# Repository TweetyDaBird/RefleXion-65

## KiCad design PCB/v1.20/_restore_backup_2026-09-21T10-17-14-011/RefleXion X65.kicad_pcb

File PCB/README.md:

# RefleXion X65

# Change Log:
- v1.00 - Initial Prototype
  - Never released.

- v1.10 - First Release
  - Total redesign for onboard RP2040 MCU
  
- v1.15 - Second Prototype
  - Never Released.
  
- v1.20 - Second Release
  - Refactored USB footprint.
  - Refactored encoder footprints.
  - Refactored switch footprints with reinforced pads(larger via).
  - Added RGB selection from Glow to Per-Key with switch.
  - Added solder/jumper to select thumb RGB layout.

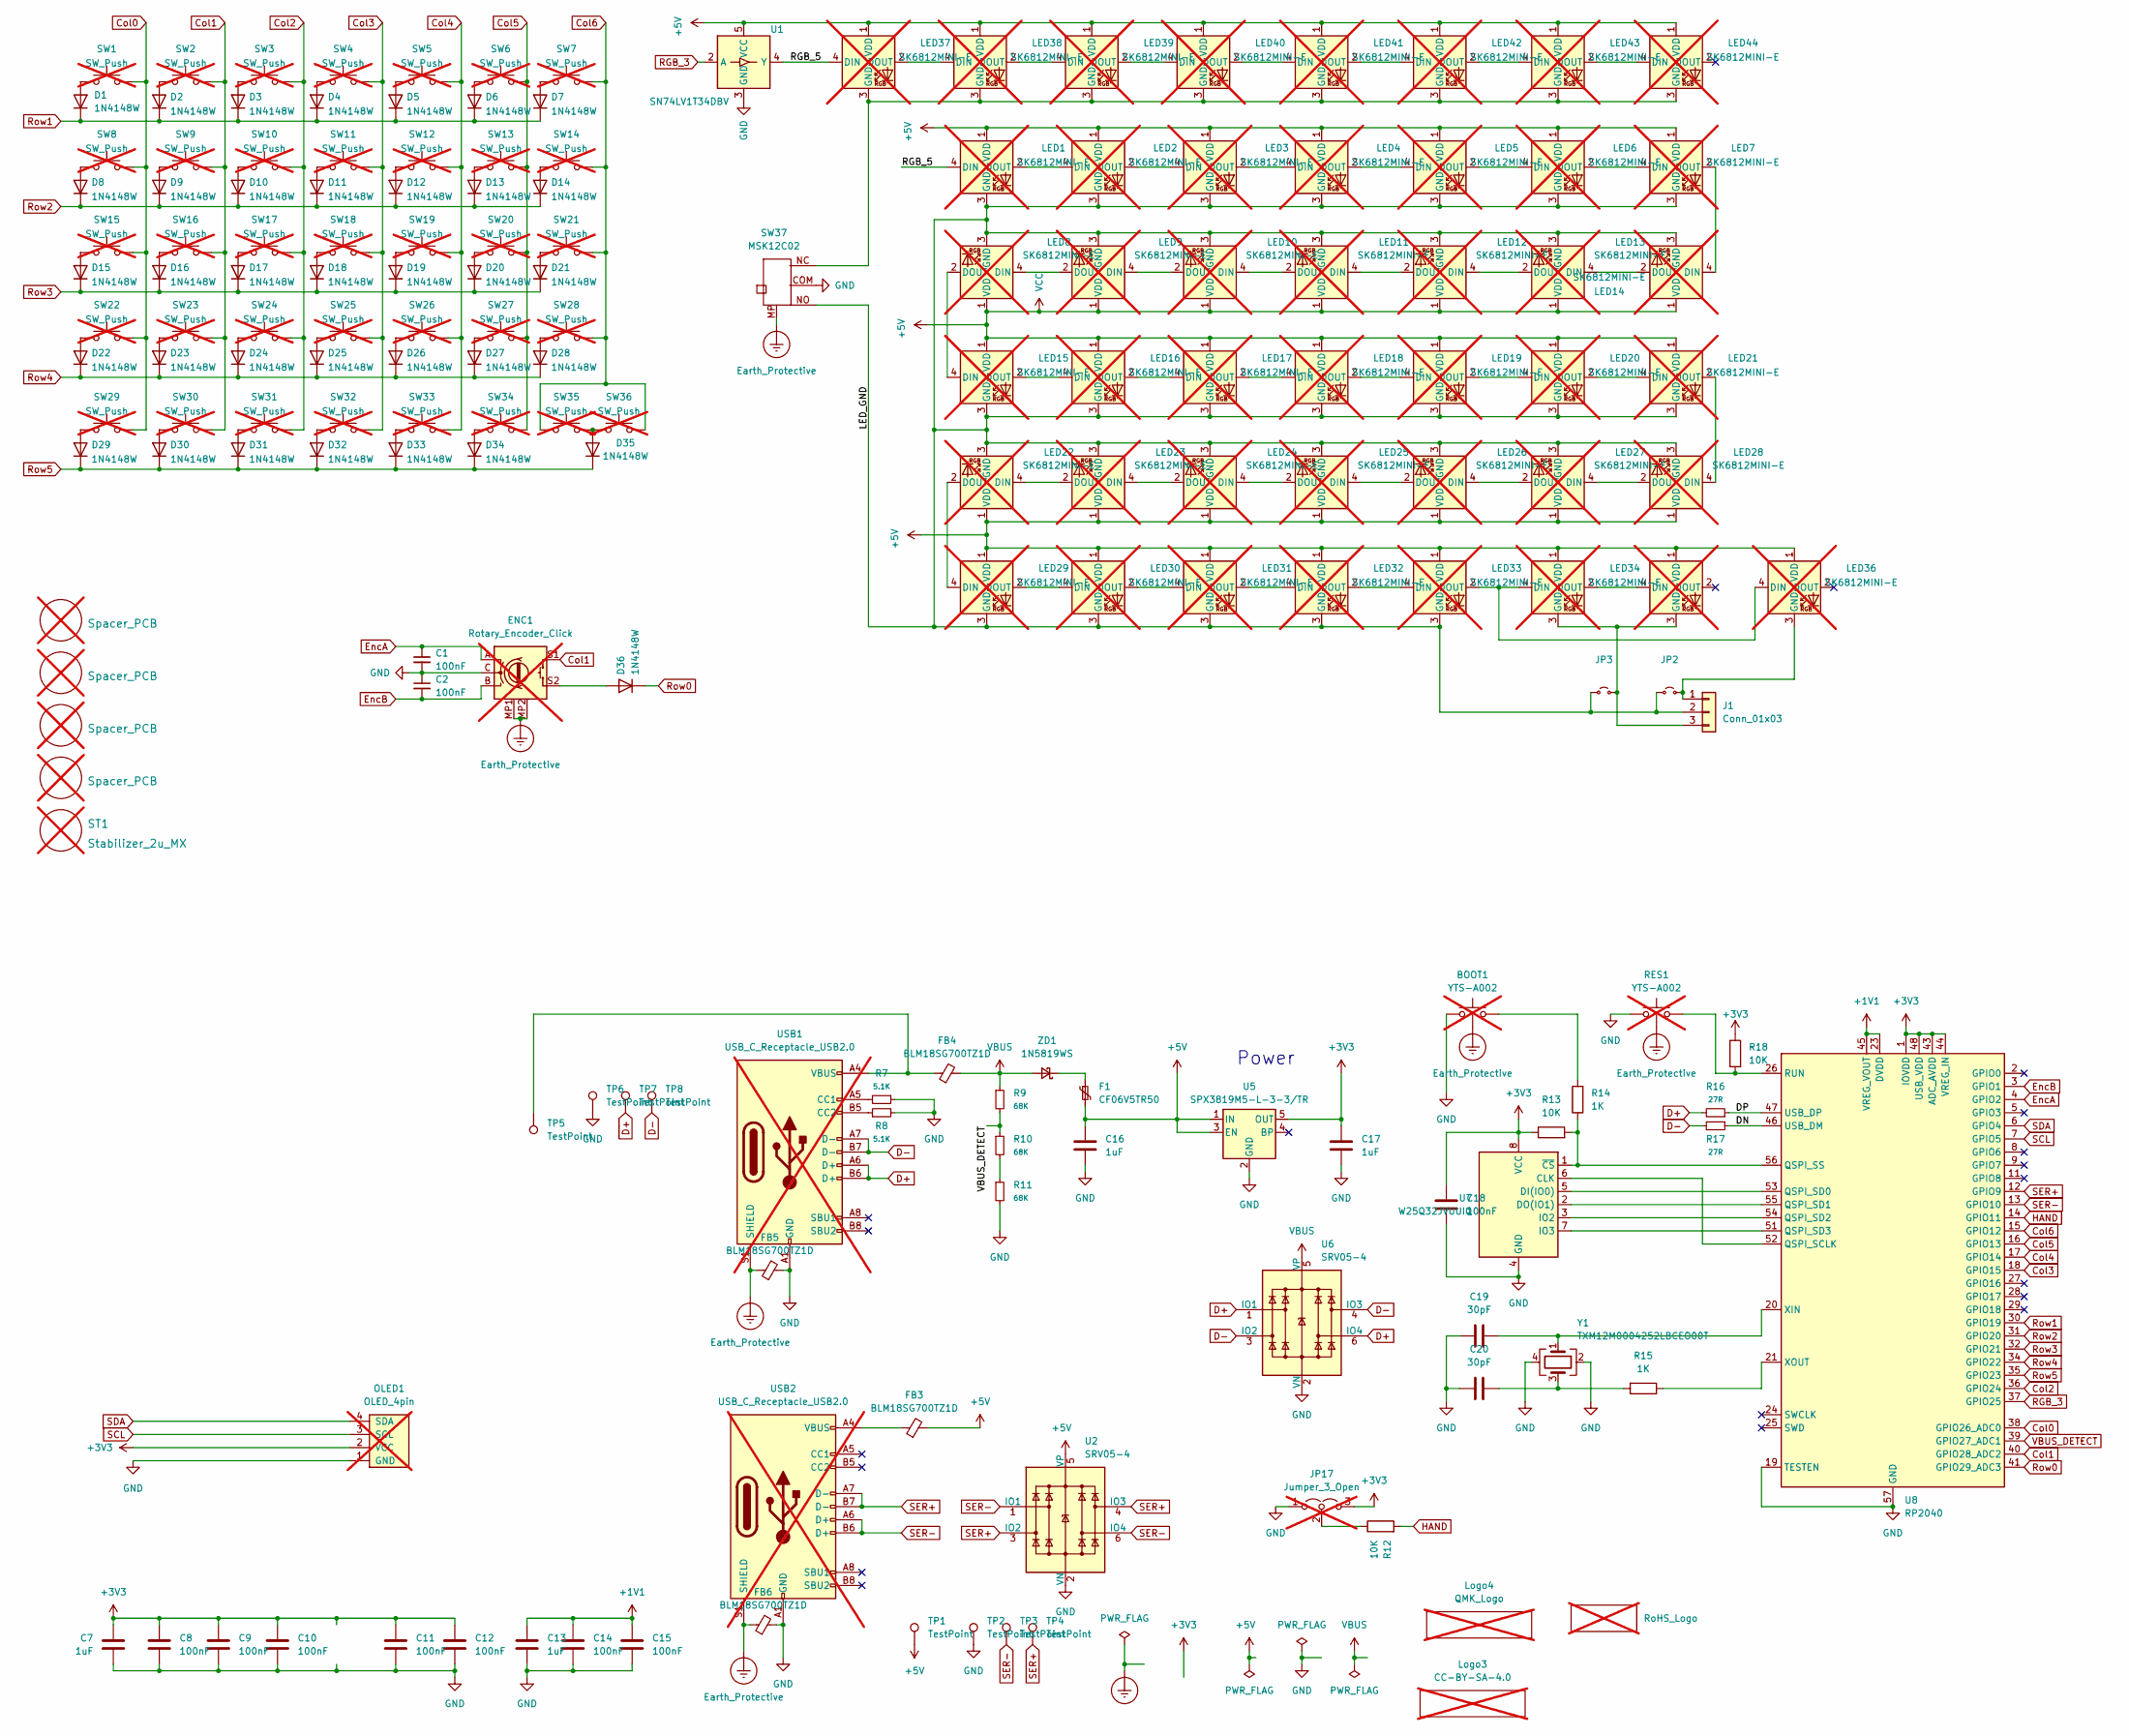
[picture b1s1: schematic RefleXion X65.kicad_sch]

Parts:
BOOT1: YTS-A002; LCSC C2910650; not fitted
C1, C2, C8, C9, C10, C11, C12, C14, C15, C18: 100nF; C_0402_1005Metric; LCSC C1525
C7, C13, C16, C17: 1uF; C_0402_1005Metric; LCSC C52923
C19, C20: 30pF; C_0402_1005Metric; LCSC C1570
D1, D2, D3, D4, D5, D6, D7, D8, D9, D10, D11, D12, D13, D14, D15, D16, D17, D18, D19, D20, D21, D22, D23, D24, D25, D26, D27, D28, D29, D30, D31, D32, D33, D34, D35, D36: 1N4148W; D_SOD-323_HandSoldering; LCSC C81598
ENC1: Rotary_Encoder_Click; Encoder_Alps_EC11E_Small; not fitted
F1: CF06V5TR50; R_0603_1608Metric; LCSC C163116
FB3, FB4, FB5, FB6: BLM18SG700TZ1D; C_0603_1608Metric_Pad1.08x0.95mm_HandSolder; LCSC C1002
H1, H2, H3, H4: Spacer_PCB; Spacer PCB hole; not fitted
J1: Conn_01x03; PinHeader_1x03_P1.27mm_Horizontal
JP2, JP3: Jumper_2_Small_Open; Jumper_min_v2
JP17: Jumper_3_Open; SolderJumper-3_open_mini; not fitted
LED1, LED2, LED3, LED4, LED5, LED6, LED7, LED8, LED9, LED10, LED11, LED12, LED13, LED14, LED15, LED16, LED17, LED18, LED19, LED20, LED21, LED22, LED23, LED24, LED25, LED26, LED27, LED28, LED29, LED30, LED31, LED32, LED33: SK6812MINI-E; MX_SK6812MINI-E_REVERSIBLE; not fitted
LED34, LED35, LED36, LED37, LED38, LED39, LED40, LED41, LED42, LED43, LED44: SK6812MINI-E; MX_SK6812MINI-E_REVERSIBLE_special; not fitted
Logo1: RoHS_Logo; RoHs; not fitted
Logo3: CC-BY-SA-4.0; CC_BY_SA_40_line; not fitted
Logo4: QMK_Logo; Powered_by_QMK; not fitted
OLED1: OLED_4pin; SSD1306-0.91-OLED-4pin-128x32 doublesided; not fitted
R7, R8: 5.1K; R_0402_1005Metric; LCSC C25905
R9, R10, R11: 68K; R_0402_1005Metric; LCSC C137947
R12, R13, R18: 10K; R_0402_1005Metric; LCSC C25744
R14, R15: 1K; R_0402_1005Metric; LCSC C11702
R16, R17: 27R; R_0402_1005Metric; LCSC C321419
RES1: YTS-A002; LCSC C2910650; not fitted
ST1: Stabilizer_2u_MX; Stabilizer_Cherry_MX_2.00u; not fitted
SW1, SW2, SW3, SW4, SW5, SW6, SW7, SW8, SW9, SW10, SW11, SW12, SW13, SW14, SW15, SW16, SW17, SW18, SW19, SW20, SW21, SW22, SW23, SW24, SW25, SW26, SW27, SW28, SW29, SW30, SW31, SW32, SW33, SW34, SW35, SW36: SW_Push; SW_MX_HotSwap_Reversible_reinforced; not fitted
SW37: MSK12C02
TP1, TP2, TP3, TP4, TP5, TP6, TP7, TP8: TestPoint; TestPoint_Pad_D1.0mm
U1: SN74LV1T34DBV; SOT-23-5; LCSC C100024
U2, U6: SRV05-4; SOT-23-6; LCSC C7420376
U5: SPX3819M5-L-3-3/TR; SOT-23-5; LCSC C9055
U7: W25Q32JVUUIQ; USON-8_4x3mm_P0.8mm; LCSC C2999380
U8: RP2040; QFN-56-1EP_7x7mm_P0.4mm_EP3.2x3.2mm_ThermalVias; LCSC C2040
USB1: USB_C_Receptacle_USB2.0; HRO_TYPE-C-31-M-12_double_sided; LCSC C963373; not fitted
USB2: USB_C_Receptacle_USB2.0; HRO_TYPE-C-31-M-12_double_sided_serial link; LCSC C963373; not fitted
Y1: TXM12M0004252LBCEO00T; Crystal_SMD_2520-4Pin_2.5x2.0mm; LCSC C284156
ZD1: 1N5819WS; D_SOD-323F; LCSC C191023

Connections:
+1V1: C13.1, C14.1, C15.1, U8.23 (DVDD), U8.45 (VREG_VOUT), U8.50 (DVDD)
+3V3: C7.1, C8.1, C9.1, C10.1, C11.1, C12.1, C17.1, C18.1, JP17.3 (B), OLED1.2 (VCC), R13.1, R18.1, U5.5 (OUT), U7.8 (VCC), U8.1 (IOVDD), U8.10 (IOVDD), U8.22 (IOVDD), U8.33 (IOVDD), U8.42 (IOVDD), U8.43 (ADC_AVDD), U8.44 (VREG_IN), U8.48 (USB_VDD), U8.49 (IOVDD)
+5V: C16.1, F1.2, FB3.2, LED1.1 (VDD), LED2.1 (VDD), LED3.1 (VDD), LED4.1 (VDD), LED5.1 (VDD), LED6.1 (VDD), LED7.1 (VDD), LED8.1 (VDD), LED9.1 (VDD), LED10.1 (VDD), LED11.1 (VDD), LED12.1 (VDD), LED13.1 (VDD), LED14.1 (VDD), LED15.1 (VDD), LED16.1 (VDD), LED17.1 (VDD), LED18.1 (VDD), LED19.1 (VDD), LED20.1 (VDD), LED21.1 (VDD), LED22.1 (VDD), LED23.1 (VDD), LED24.1 (VDD), LED25.1 (VDD), LED26.1 (VDD), LED27.1 (VDD), LED28.1 (VDD), LED29.1 (VDD), LED30.1 (VDD), LED31.1 (VDD), LED32.1 (VDD), LED33.1 (VDD), LED34.1 (VDD), LED35.1 (VDD), LED36.1 (VDD), LED37.1 (VDD), LED38.1 (VDD), LED39.1 (VDD), LED40.1 (VDD), LED41.1 (VDD), LED42.1 (VDD), LED43.1 (VDD), LED44.1 (VDD), TP1.1 (1_1), U1.5 (VCC), U2.5 (VP), U5.1 (IN), U5.3 (EN)
/DN: R17.1, U8.46 (USB_DM)
/DP: R16.1, U8.47 (USB_DP)
/LED_GND: J1.2, JP2.1 (A), JP3.1 (A), LED1.3 (GND), LED2.3 (GND), LED3.3 (GND), LED4.3 (GND), LED5.3 (GND), LED6.3 (GND), LED7.3 (GND), LED8.3 (GND), LED9.3 (GND), LED10.3 (GND), LED11.3 (GND), LED12.3 (GND), LED13.3 (GND), LED14.3 (GND), LED15.3 (GND), LED16.3 (GND), LED17.3 (GND), LED18.3 (GND), LED19.3 (GND), LED20.3 (GND), LED21.3 (GND), LED22.3 (GND), LED23.3 (GND), LED24.3 (GND), LED25.3 (GND), LED26.3 (GND), LED27.3 (GND), LED28.3 (GND), LED29.3 (GND), LED30.3 (GND), LED31.3 (GND), LED32.3 (GND), LED33.3 (GND), SW37.NO
/RGB_5: LED1.4 (DIN), LED37.4 (DIN), U1.4 (Y)
Col0: SW1.1, SW8.1, SW15.1, SW22.1, SW29.1, U8.38 (GPIO26_ADC0)
Col1: ENC1.S1, SW2.2, SW9.2, SW16.2, SW23.2, SW30.2, U8.40 (GPIO28_ADC2)
Col2: SW3.2, SW10.2, SW17.2, SW24.2, SW31.2, U8.36 (GPIO24)
Col3: SW4.2, SW11.2, SW18.2, SW25.2, SW32.2, U8.18 (GPIO15)
Col4: SW5.2, SW12.2, SW19.2, SW26.2, SW33.2, U8.17 (GPIO14)
Col5: SW6.2, SW13.2, SW20.2, SW27.2, SW34.2, U8.16 (GPIO13)
Col6: SW7.2, SW14.2, SW21.2, SW28.2, SW35.1, SW36.2, U8.15 (GPIO12)
D+: R16.2, TP7.1 (1_1), U6.1 (IO1), U6.6 (IO4), USB1.A6 (D+), USB1.B6 (D+)
D-: R17.2, TP8.1 (1_1), U6.3 (IO2), U6.4 (IO3), USB1.A7 (D-), USB1.B7 (D-)
Earth_Protective: BOOT1.3, ENC1.MP1 (GND), ENC1.MP2 (GND), FB5.1, FB6.1, RES1.3, SW37.MP (GND), USB1.S1 (SHIELD), USB2.S1 (SHIELD)
Enc1: D1.2 (A), SW1.2
Enc2: D7.2 (A), SW7.1
EncA: C1.1, ENC1.A, U8.4 (GPIO2)
EncB: C2.2, ENC1.B, U8.3 (GPIO1)
GND: BOOT1.2, C1.2, C2.1, C7.2, C8.2, C9.2, C10.2, C11.2, C12.2, C13.2, C14.2, C15.2, C16.2, C17.2, C18.2, C19.2, C20.2, ENC1.C, FB5.2, FB6.2, JP17.1 (A), OLED1.1 (GND), R7.1, R8.2, R11.2, RES1.1, SW37.COM, TP2.1 (1_1), TP6.1 (1_1), U1.3 (GND), U2.2 (VN), U5.2 (GND), U6.2 (VN), U7.4 (GND), U8.19 (TESTEN), U8.57 (GND), USB1.A1 (GND), USB1.A12 (GND), USB1.B1 (GND), USB1.B12 (GND), USB2.A1 (GND), USB2.A12 (GND), USB2.B1 (GND), USB2.B12 (GND), Y1.2, Y1.4
HAND: R12.2, U8.14 (GPIO11)
unnamed: BOOT1.1, R14.2
unnamed: C20.1, R15.2, Y1.3
unnamed: D2.2 (A), SW2.1
unnamed: D3.2 (A), SW3.1
unnamed: D4.2 (A), SW4.1
unnamed: D5.2 (A), SW5.1
unnamed: D6.2 (A), SW6.1
unnamed: D8.2 (A), SW8.2
unnamed: D9.2 (A), SW9.1
unnamed: D10.2 (A), SW10.1
unnamed: D11.2 (A), SW11.1
unnamed: D12.2 (A), SW12.1
unnamed: D13.2 (A), SW13.1
unnamed: D14.2 (A), SW14.1
unnamed: D15.2 (A), SW15.2
unnamed: D16.2 (A), SW16.1
unnamed: D17.2 (A), SW17.1
unnamed: D18.2 (A), SW18.1
unnamed: D19.2 (A), SW19.1
unnamed: D20.2 (A), SW20.1
unnamed: D21.2 (A), SW21.1
unnamed: D22.2 (A), SW22.2
unnamed: D23.2 (A), SW23.1
unnamed: D24.2 (A), SW24.1
unnamed: D25.2 (A), SW25.1
unnamed: D26.2 (A), SW26.1
unnamed: D27.2 (A), SW27.1
unnamed: D28.2 (A), SW28.1
unnamed: D29.2 (A), SW29.2
unnamed: D30.2 (A), SW30.1
unnamed: D31.2 (A), SW31.1
unnamed: D32.2 (A), SW32.1
unnamed: D33.2 (A), SW33.1
unnamed: D34.2 (A), SW34.1
unnamed: D35.2 (A), SW35.2, SW36.1
unnamed: D36.2 (A), ENC1.S2
unnamed: FB3.1, USB2.A4 (VBUS), USB2.A9 (VBUS), USB2.B4 (VBUS), USB2.B9 (VBUS)
unnamed: FB4.1, TP5.1 (1_1), USB1.A4 (VBUS), USB1.A9 (VBUS), USB1.B4 (VBUS), USB1.B9 (VBUS)
unnamed: J1.1, JP2.2 (B), LED36.3 (GND)
unnamed: J1.3, JP3.2 (B), LED34.3 (GND), LED35.3 (GND)
unnamed: JP17.2 (C), R12.1
unnamed: LED1.2 (DOUT), LED2.4 (DIN)
unnamed: LED2.2 (DOUT), LED3.4 (DIN)
unnamed: LED3.2 (DOUT), LED4.4 (DIN)
unnamed: LED4.2 (DOUT), LED5.4 (DIN)
unnamed: LED5.2 (DOUT), LED6.4 (DIN)
unnamed: LED6.2 (DOUT), LED7.4 (DIN)
unnamed: LED8.4 (DIN), LED9.2 (DOUT)
unnamed: LED10.4 (DIN), LED11.2 (DOUT)
unnamed: LED9.4 (DIN), LED10.2 (DOUT)
unnamed: LED11.4 (DIN), LED12.2 (DOUT)
unnamed: LED12.4 (DIN), LED13.2 (DOUT)
unnamed: LED13.4 (DIN), LED14.2 (DOUT)
unnamed: LED7.2 (DOUT), LED14.4 (DIN)
unnamed: LED8.2 (DOUT), LED15.4 (DIN)
unnamed: LED15.2 (DOUT), LED16.4 (DIN)
unnamed: LED16.2 (DOUT), LED17.4 (DIN)
unnamed: LED17.2 (DOUT), LED18.4 (DIN)
unnamed: LED18.2 (DOUT), LED19.4 (DIN)
unnamed: LED19.2 (DOUT), LED20.4 (DIN)
unnamed: LED20.2 (DOUT), LED21.4 (DIN)
unnamed: LED21.2 (DOUT), LED28.4 (DIN)
unnamed: LED22.4 (DIN), LED23.2 (DOUT)
unnamed: LED22.2 (DOUT), LED29.4 (DIN)
unnamed: LED23.4 (DIN), LED24.2 (DOUT)
unnamed: LED24.4 (DIN), LED25.2 (DOUT)
unnamed: LED25.4 (DIN), LED26.2 (DOUT)
unnamed: LED26.4 (DIN), LED27.2 (DOUT)
unnamed: LED27.4 (DIN), LED28.2 (DOUT)
unnamed: LED29.2 (DOUT), LED30.4 (DIN)
unnamed: LED30.2 (DOUT), LED31.4 (DIN)
unnamed: LED31.2 (DOUT), LED32.4 (DIN)
unnamed: LED32.2 (DOUT), LED33.4 (DIN)
unnamed: LED33.2 (DOUT), LED34.4 (DIN), LED36.4 (DIN)
unnamed: LED34.2 (DOUT), LED35.4 (DIN)
unnamed: LED37.2 (DOUT), LED38.4 (DIN)
unnamed: LED37.3 (GND), LED38.3 (GND), LED39.3 (GND), LED40.3 (GND), LED41.3 (GND), LED42.3 (GND), LED43.3 (GND), LED44.3 (GND), SW37.NC
unnamed: LED38.2 (DOUT), LED39.4 (DIN)
unnamed: LED39.2 (DOUT), LED40.4 (DIN)
unnamed: LED40.2 (DOUT), LED41.4 (DIN)
unnamed: LED41.2 (DOUT), LED42.4 (DIN)
unnamed: LED42.2 (DOUT), LED43.4 (DIN)
unnamed: LED43.2 (DOUT), LED44.4 (DIN)
unnamed: R10.2, R11.1
unnamed: U7.6 (CLK), U8.52 (QSPI_SCLK)
unnamed: U7.5 (DI(IO0)), U8.53 (QSPI_SD0)
unnamed: U7.2 (DO(IO1)), U8.55 (QSPI_SD1)
unnamed: U7.3 (IO2), U8.54 (QSPI_SD2)
unnamed: U7.7 (IO3), U8.51 (QSPI_SD3)
unnamed: R13.2, R14.1, U7.1 (~CS), U8.56 (QSPI_SS)
unnamed: R18.2, RES1.2, U8.26 (RUN)
unnamed: C19.1, U8.20 (XIN), Y1.1
unnamed: R15.1, U8.21 (XOUT)
unnamed: R7.2, USB1.A5 (CC1)
unnamed: R8.1, USB1.B5 (CC2)
unnamed: F1.1, ZD1.1 (K)
RGB_3: U1.2 (A), U8.37 (GPIO25)
Row0: D36.1 (K), U8.41 (GPIO29_ADC3)
Row1: D1.1 (K), D2.1 (K), D3.1 (K), D4.1 (K), D5.1 (K), D6.1 (K), D7.1 (K), U8.30 (GPIO19)
Row2: D8.1 (K), D9.1 (K), D10.1 (K), D11.1 (K), D12.1 (K), D13.1 (K), D14.1 (K), U8.31 (GPIO20)
Row3: D15.1 (K), D16.1 (K), D17.1 (K), D18.1 (K), D19.1 (K), D20.1 (K), D21.1 (K), U8.32 (GPIO21)
Row4: D22.1 (K), D23.1 (K), D24.1 (K), D25.1 (K), D26.1 (K), D27.1 (K), D28.1 (K), U8.34 (GPIO22)
Row5: D29.1 (K), D30.1 (K), D31.1 (K), D32.1 (K), D33.1 (K), D34.1 (K), D35.1 (K), U8.35 (GPIO23)
SCL: OLED1.3 (SCL), U8.7 (GPIO5)
SDA: OLED1.4 (SDA), U8.6 (GPIO4)
SER+: TP4.1 (1_1), U2.3 (IO2), U2.4 (IO3), U8.12 (GPIO9), USB2.A7 (D-), USB2.B7 (D-)
SER-: TP3.1 (1_1), U2.1 (IO1), U2.6 (IO4), U8.13 (GPIO10), USB2.A6 (D+), USB2.B6 (D+)
VBUS: FB4.2, R9.1, U6.5 (VP), ZD1.2 (A)
VBUS_DETECT: R9.2, R10.1, U8.39 (GPIO27_ADC1)

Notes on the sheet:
Power

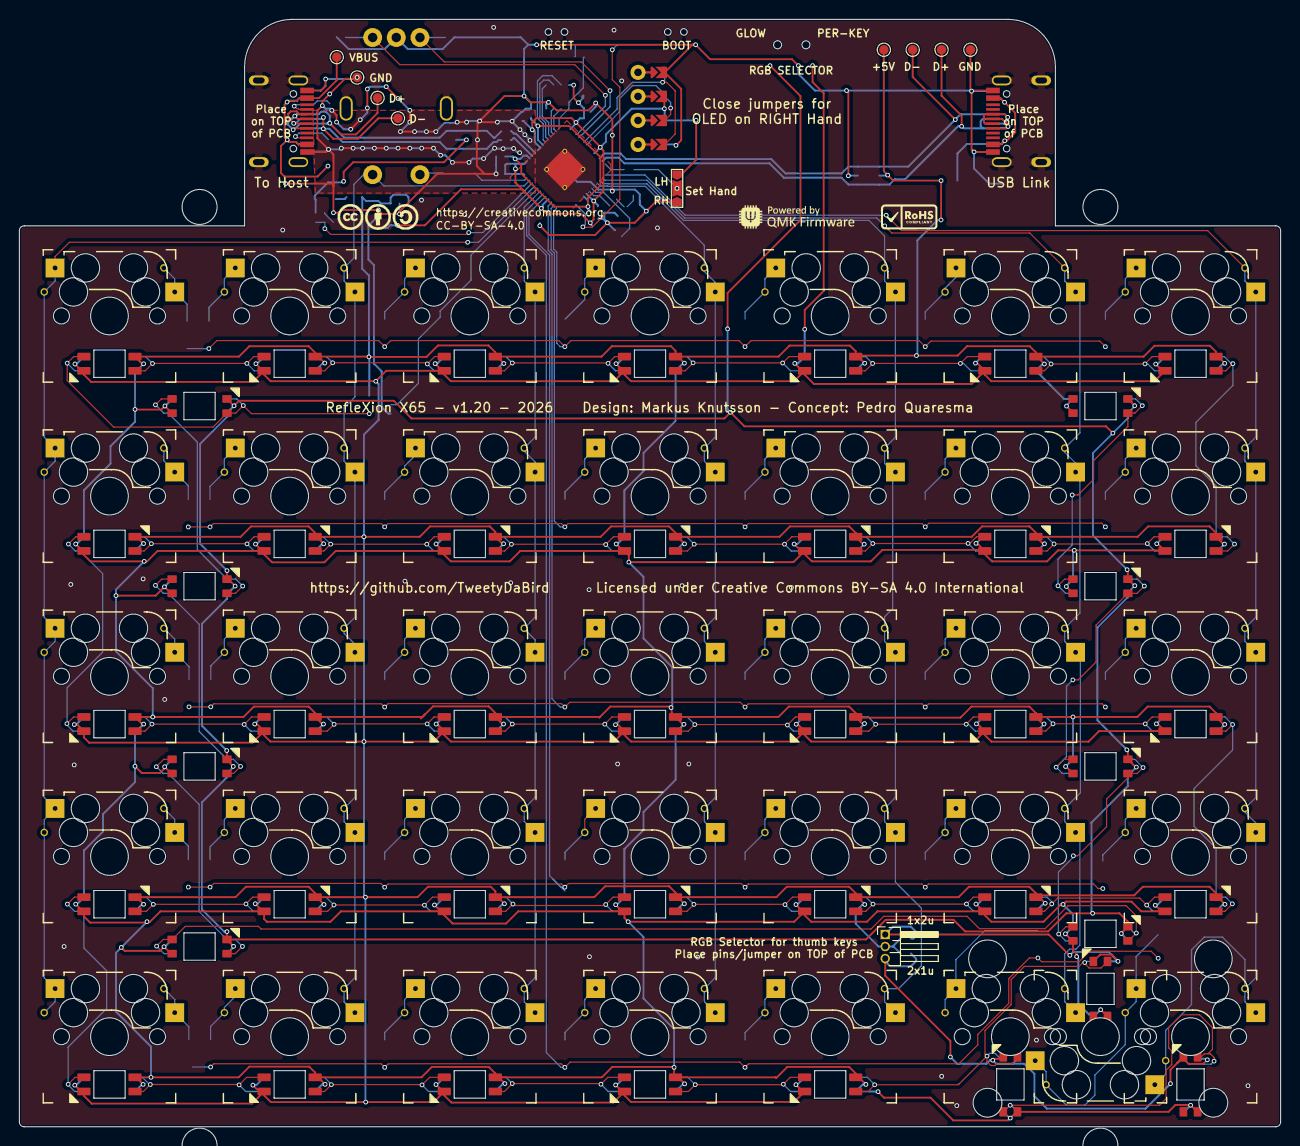
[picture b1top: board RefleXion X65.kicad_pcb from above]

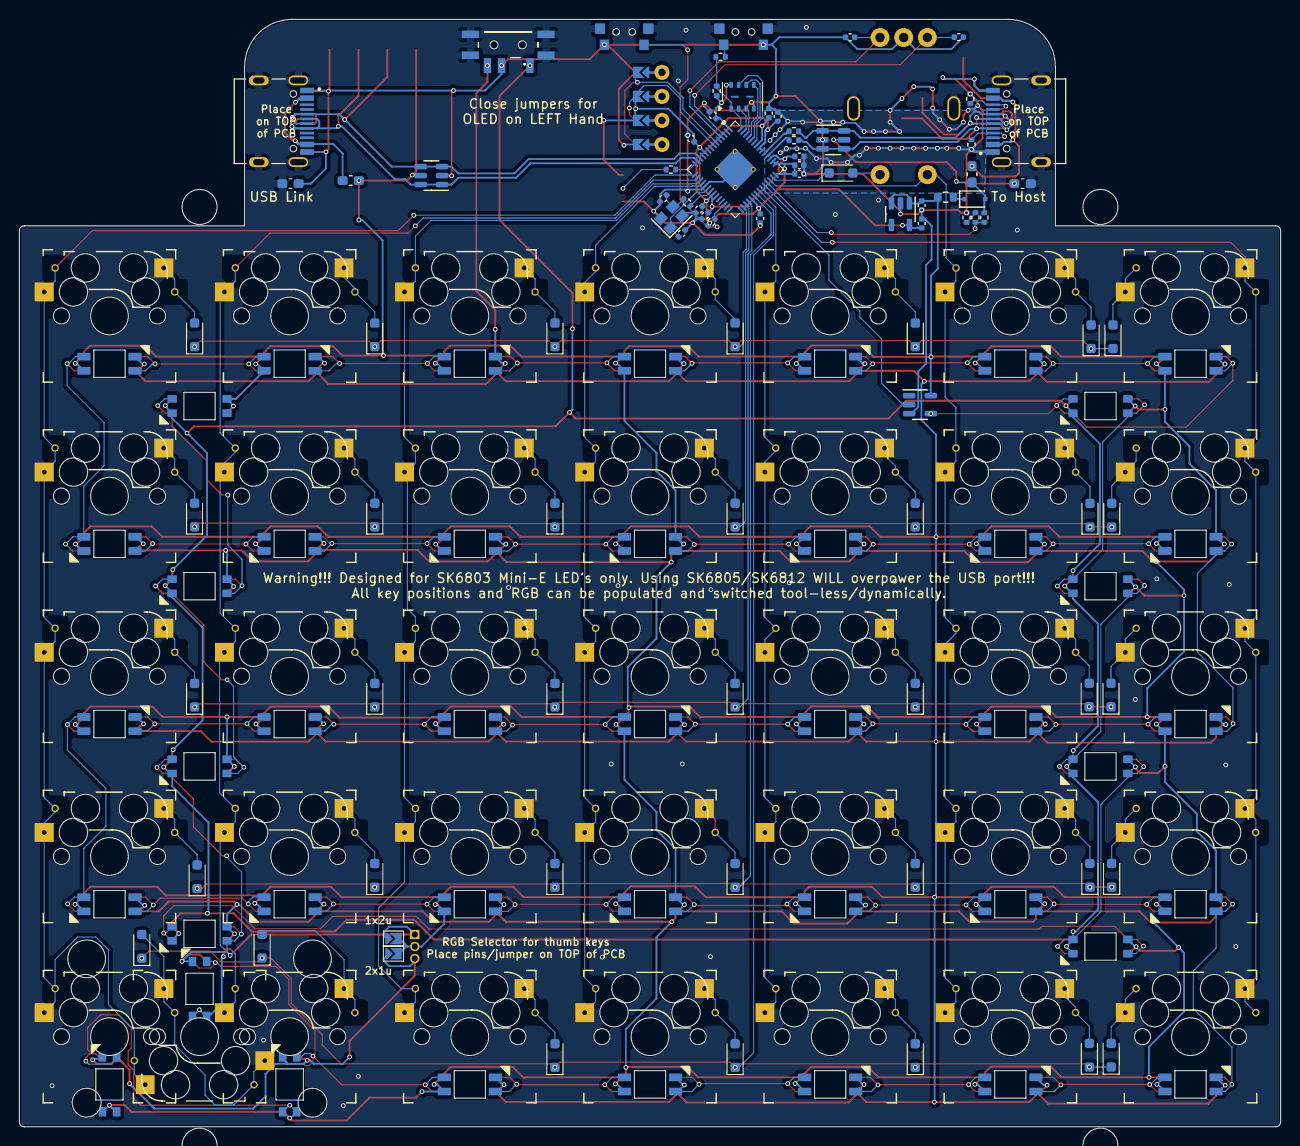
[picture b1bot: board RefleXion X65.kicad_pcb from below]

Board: 2 copper layers, 133.4 x 117.1 mm, 184 parts (84 on the bottom side), 132 nets.

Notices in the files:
PCB/v1.10/RefleXion X65.kicad_sch:
Licensed under Creative Commons BY-SA 4.0 International
